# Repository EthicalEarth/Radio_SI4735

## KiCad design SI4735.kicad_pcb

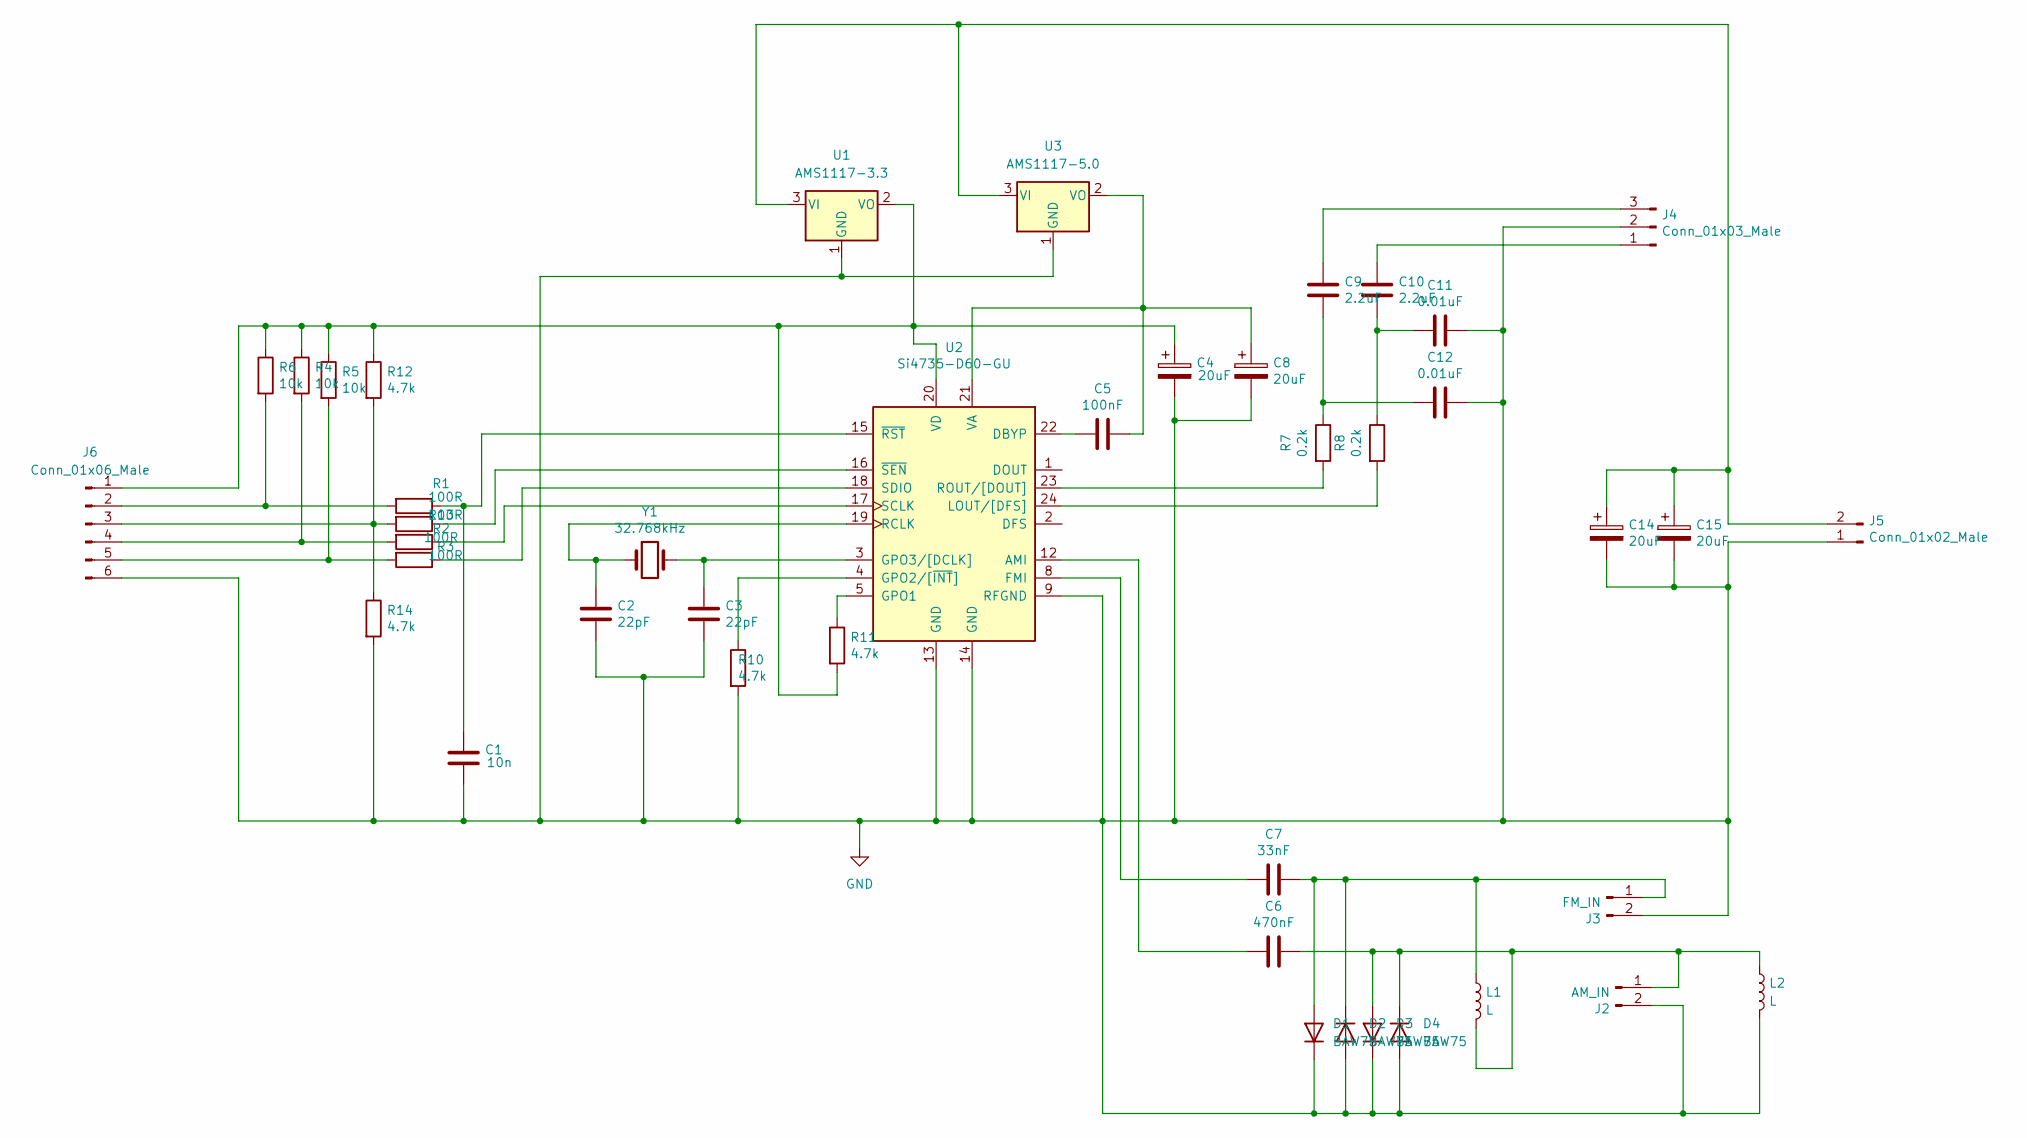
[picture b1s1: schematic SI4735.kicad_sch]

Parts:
C1: 10n; C_1206_3216Metric
C2, C3: 22pF; C_1206_3216Metric
C4, C8, C14, C15: 20uF; CP_Radial_D5.0mm_P2.00mm
C5: 100nF; C_Disc_D3.0mm_W1.6mm_P2.50mm
C6: 470nF; C_Disc_D4.3mm_W1.9mm_P5.00mm
C7: 33nF; C_Disc_D4.3mm_W1.9mm_P5.00mm
C9, C10: 2.2uF; C_Disc_D3.4mm_W2.1mm_P2.50mm
C11, C12: 0.01uF; C_Disc_D3.4mm_W2.1mm_P2.50mm
D1, D2, D3, D4: BAW75; D_DO-35_SOD27_P7.62mm_Horizontal
J2: AM_IN; SMA_Amphenol_901-143_Horizontal
J3: FM_IN; SMA_Amphenol_901-143_Horizontal
J4: Conn_01x03_Male; PinHeader_1x03_P2.54mm_Vertical
J5: Conn_01x02_Male; PinHeader_1x02_P2.54mm_Vertical
J6: Conn_01x06_Male; PinHeader_1x06_P2.54mm_Vertical
L1, L2: L; L_Radial_D6.0mm_P4.00mm
R1, R2, R3, R13: 100R; R_1206_3216Metric
R4, R5, R6: 10k; R_1206_3216Metric
R7, R8: 0.2k; R_1206_3216Metric
R10, R12, R14: 4.7k; R_1206_3216Metric
R11: 4.7k; R_Axial_DIN0309_L9.0mm_D3.2mm_P12.70mm_Horizontal
U1: AMS1117-3.3; SOT-223-3_TabPin2
U2: Si4735-D60-GU; SSOP-24_3.9x8.7mm_P0.635mm
U3: AMS1117-5.0; SOT-223-3_TabPin2
Y1: 32.768kHz; Crystal_Round_D3.0mm_Vertical

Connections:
GND: C1.2, C2.2, C3.2, C4.2, C8.2, C11.1, C12.1, C14.2, C15.2, D1.1 (K), D2.2 (A), D3.1 (K), D4.2 (A), J2.2, J3.2, J4.2, J5.1, J6.6, L2.2, R10.2, R14.2, U1.1 (GND), U2.9 (RFGND), U2.13 (GND), U2.14 (GND), U3.1 (GND)
unnamed: C10.2, C11.2, R8.1
unnamed: C9.2, C12.2, R7.1
unnamed: C7.1, D1.2 (A), D2.1 (K), J3.1, L1.1
unnamed: C6.1, D3.2 (A), D4.1 (K), J2.1, L1.2, L2.1
unnamed: C10.1, J4.1
unnamed: C9.1, J4.3
unnamed: C14.1, C15.1, J5.2, U1.3 (VI), U3.3 (VI)
unnamed: C4.1, J6.1, R4.1, R5.1, R6.1, R11.2, R12.1, U1.2 (VO), U2.20 (VD)
unnamed: J6.2, R1.2, R6.2
unnamed: J6.3, R12.2, R13.2, R14.1
unnamed: J6.4, R2.2, R4.2
unnamed: J6.5, R3.2, R5.2
unnamed: C6.2, U2.12 (AMI)
unnamed: C5.2, U2.22 (DBYP)
unnamed: C7.2, U2.8 (FMI)
unnamed: R11.1, U2.5 (GPO1)
unnamed: R10.1, U2.4 (GPO2/[~INT])
unnamed: C3.1, U2.3 (GPO3/[DCLK]), Y1.2
unnamed: R8.2, U2.24 (LOUT/[DFS])
unnamed: C2.1, U2.19 (RCLK), Y1.1
unnamed: R7.2, U2.23 (ROUT/[DOUT])
unnamed: R2.1, U2.17 (SCLK)
unnamed: R3.1, U2.18 (SDIO)
unnamed: C5.1, C8.1, U2.21 (VA), U3.2 (VO)
unnamed: C1.1, R1.1, U2.15 (~RST)
unnamed: R13.1, U2.16 (~SEN)

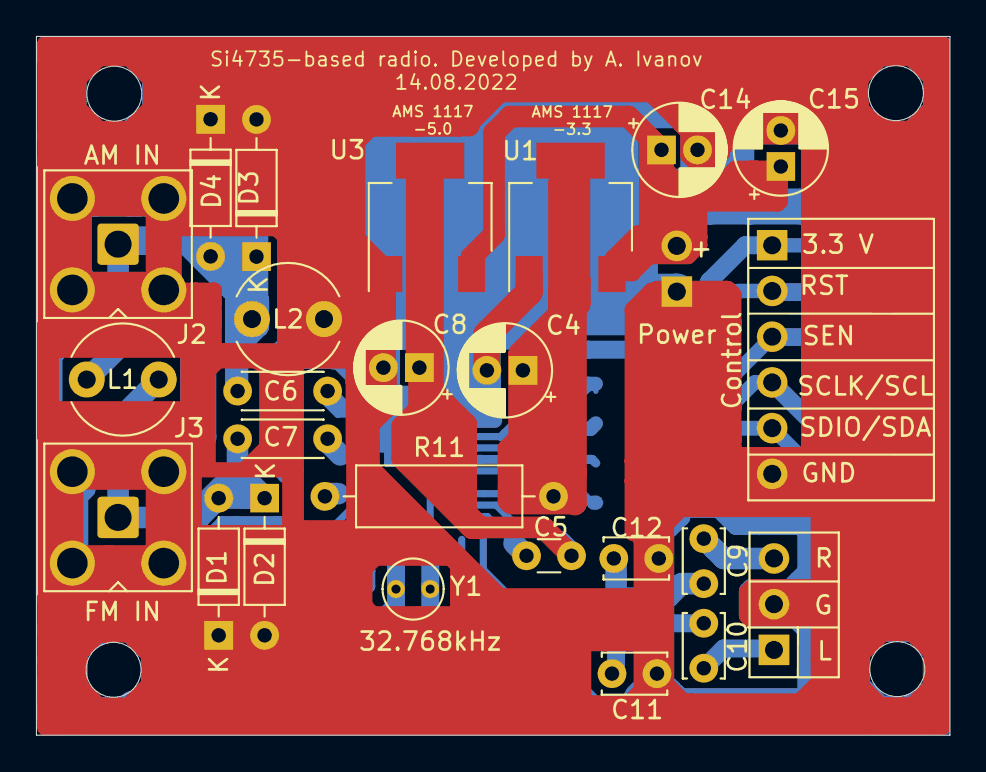
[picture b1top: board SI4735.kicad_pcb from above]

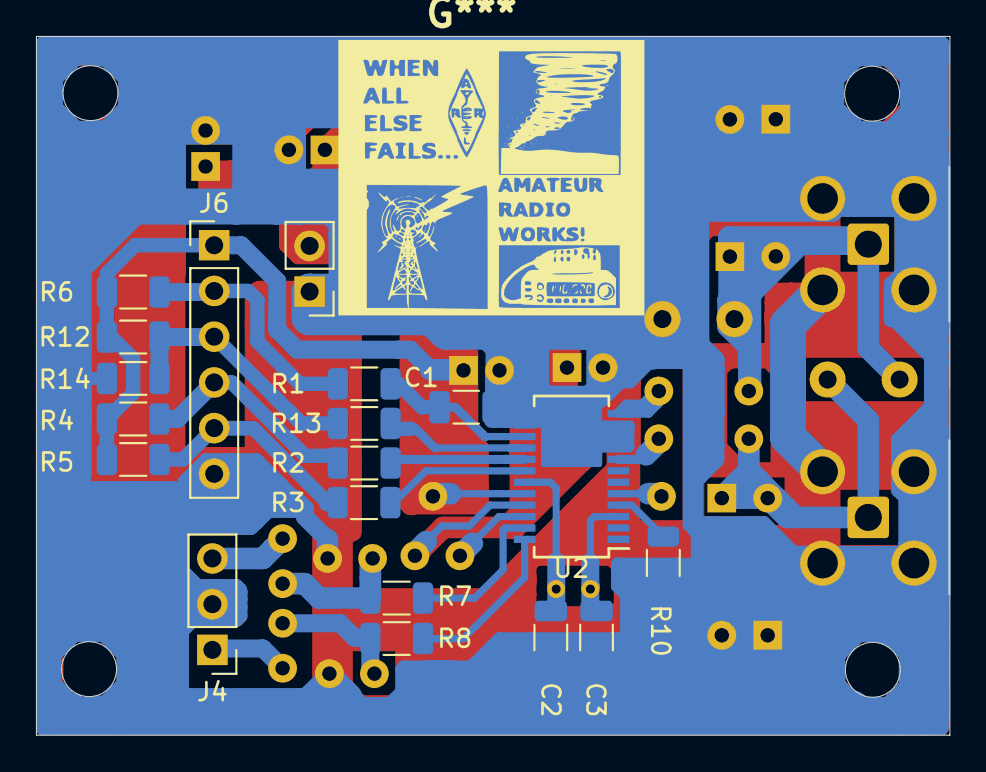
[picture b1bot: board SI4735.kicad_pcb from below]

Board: 2 copper layers, 50.8 x 38.8 mm, 42 parts (19 on the bottom side), 27 nets.

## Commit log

2023-11-05 Update Project Data
2024-03-27 recovering the project
